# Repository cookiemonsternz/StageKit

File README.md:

# Stagekit

Stagekit is a 3D-printable, completely hand-solderable diy lighting previs kit. 

It consists of various fixtures, truss elements, and set dressing pieces, all modelled at a fairly accurate 1:10 scale. The truss pieces are modelled after standard Eurotruss, and the lights after various fixtures, but due to design requirements, sizing and design liberties have had to be taken. 

The inspiration for the design was really just the limited visualisation tools available for hobbyist lighting designers. There's certainly a lot of software, but much of it is prohibitively expensive, especially for students, then of course, comes the question of having software that can actually output to it. Guess what, you have to pay for that too. 

## Fixtures

Currently, Stagekit has 3 fixture designs available, but more designs are coming in the future.

| Fixture     | Estimated Material Cost (USD) | Images                               |
|-------------|-------------------------------| ------------------------------------ |
| RGB Par     | $4                            |  |
| RGB Tube    | $5                            |     |
| RGB Blinder | $4                            |  |

The RGB Blinder and RGB Tube both utilize neopixels, and the RGB Par uses a RGB Led. All fixtures use an ATTiny85 acting as an i2c slave, controlled by a RPi Zero 2 W or other i2c capable controller. The controller acts as an art net node, and sends i2c over 4 wire Molex Picoblade connectors, daisy chained together akin to DMX.

## Truss Pieces

There are currently four main truss pieces available, with more options in the future again.
All parts should be easily printable, and there are versions of each file which should be able to be printed without supports. 

Truss piece straight - 100mm

Truss piece corner

Truss base piece

Truss connector bracket

## Set elements

There are a variety of set pieces available.
Ashdown ABM-600 EVO IV:

Ampeg Classic 8x10 Cab:

Fender Rumble 100:

Markbass 1x15 cab:

Generic 4x10 cab:

Generic Roadcase:

Generic Wedge Monitor:

Generic Subwoofer:

Generic Line Array:

*Note: scale should be checked before printing, while this is to scale, it is very large*

Generic Fence:

Stage platform 1x1:

Stage platform 1x2:

Stage platform 2x2:

Stage stairs:

Finally, an example miniature stage mockup:

## Firmware

To program the ATTiny85 chips, you will need either a dedicated programmer or an Arduino Uno or similar. The source code for all of the lights can be found in the firmware directory.

Unfortunately, due to size and budget limitations, light addresses must be hardcoded into each chip individually. This means that when flashing firmware, ensure each light has a different address assigned, by editing the `.ino` file and changing the value of `I2C_SLAVE_ADDRESS` to any unused value between 0x01 and 0x7F before programming.

PCB Source files can be found in the respective folder (Blinder, RGB Par, RGB Tube) and all 3D models can be found inside the cad folder.

## PCB Pictures for Highway

RGB Par:

RGB Tube:

Blinder:

## BOM

Better formatted BOM's are also available at [this google sheet](https://docs.google.com/spreadsheets/d/1baBuS65jXXmk7wej5hXxSFTJ-pqP7fWwTh28TKW3xLs).

**RGB PAR**
| Item       | Part Name       | Quantity | Source     | Link                                                  | Unit Cost | Total Cost | Notes                                                                                                                                                                                            |
|------------|-----------------|----------|------------|-------------------------------------------------------|-----------|------------|--------------------------------------------------------------------------------------------------------------------------------------------------------------------------------------------------|
| U1         | ATTiny85        | 1        | Aliexpress | https://www.aliexpress.com/item/1005007400913382.html | 1.75      | 1.75       | Looking for cheaper ones                                                                                                                                                                         |
| D1         | RGB LED         | 1        | Aliexpress | https://www.aliexpress.com/item/1005005768279384.html | 0.46      | 0.46       | I have designed this for the 3x3w 6 pin rgb, as that is what I had on hand, but the 3x1w 6 pin rgb will almost certainly work as well, and the led driver does not even close to deliver 3 watts |
| R1         | 150Ω Resistor   | 1        | Aliexpress | https://www.aliexpress.com/item/1005001627995396.html | 0.02      | 0.02       | Comes in pack of 100, 1.65 per resistor value                                                                                                                                                    |
| R2, R3     | 100Ω Resistor   | 2        | Aliexpress | https://www.aliexpress.com/item/1005001627995396.html | 0.02      | 0.04       | Comes in pack of 100, 1.65 per resistor value                                                                                                                                                    |
| R4         | 10KΩ Resistor   | 1        | Aliexpress | https://www.aliexpress.com/item/1005001627995396.html | 0.02      | 0.02       | Comes in pack of 100, 1.65 per resistor value                                                                                                                                                    |
| J1, J3     | Molex Conn      | 2        | Aliexpress | https://aliexpress.com/item/4000127192324.html        | 0.06      | 0.12       | If you buy more than 50 you can bring this down to a total cost of 0.16                                                                                                                          |
| PCB        | PCB             | 1        | JLCPCB     | https://jlcpcb.com/                                   | 0.42      | 0.42       |                                                                                                                                                                                                  |
| CASEB      | Bottom Case     | 1        | 3D Printed | NA                                                    | 0.08      | 0.08       | around 4g of filament, if done through jlc3dp with standard resin, costs 0.36                                                                                                                    |
| CASET      | Top Case        | 1        | 3D Printed | NA                                                    | 0.04      | 0.04       | If printed on fdm printer, its approx 2g of filament, if ordered through jlcpcb with standard resin, cost 0.3 (min possible)                                                                     |
| PAPER      | Diffusion Paper | 1        | NA         | NA                                                    | NA        | NA         | The diffusion paper can be any semi transparent paper like material, I'm using white baking paper, and thus have ommitted the cost as it feels pointless to measure this                         |
| Total Cost |                 |          |            |                                                       |           |            |                                                                                                                                                                                                  |
|            |                 |          |            |                                                       |           | 2.95       | Economy of scale does come into play here, especially with the attiny and the pcbs                                                                                                               |

**RGB Tube**
| Item                   | Part Name       | Quantity | Source     | Link                                                  | Unit Cost | Total Cost | Notes                                                                                                                                                                                                                    |
|------------------------|-----------------|----------|------------|-------------------------------------------------------|-----------|------------|--------------------------------------------------------------------------------------------------------------------------------------------------------------------------------------------------------------------------|
| U1                     | ATTiny85        | 1        | Aliexpress | https://www.aliexpress.com/item/1005007400913382.html | 1.75      | 1.75       | Looking for cheaper ones                                                                                                                                                                                                 |
| R4                     | 10KΩ Resistor   | 1        | Aliexpress | https://www.aliexpress.com/item/1005001627995396.html | 0.02      | 0.02       | Comes in pack of 100, 1.65 per resistor value                                                                                                                                                                            |
| J1, J2                 | Molex Conn      | 2        | Aliexpress | https://aliexpress.com/item/4001254843951.html        | 0.04      | 0.08       | This is for 100 unfortunately, but I can't find anything else on aliexpress and lcsc shipping is insane                                                                                                                  |
| D1, D2, D3, D4, D5, D6 | Neopixel        | 6        | Aliexpress | https://www.aliexpress.com/item/4001345875756.html    | 0.03      | 0.18       | This is assuming ordering a batch of 100                                                                                                                                                                                 |
| PCB                    | PCB             | 1        | JLCPCB     | https://jlcpcb.com/                                   | 0.84      | 0.84       | Batch of five                                                                                                                                                                                                            |
| CASEB                  | Bottom Case     | 1        | 3D Printed | NA                                                    | NA        | NA         | Cura says 0g of filament lol, if done through jlc3dp with standard resin, cost 0.3                                                                                                                                       |
| CASET1                 | Top Case Body   | 1        | 3D Printed | NA                                                    | 0.05      | 0.05       | around 3g of filament, if done through jlc3dp with standard resin, costs 0.30. This piece includes the clamp connected to the print, but it can also be printed seperately                                               |
| CASET2                 | Top Case Cap    | 1        | 3D Printed | NA                                                    | NA        | NA         | Again, 0g of filament, will also cost 0.3 because that is the minimum cost                                                                                                                                               |
| TUBE                   | PMMA Tube       | 1        | Aliexpress | https://www.aliexpress.com/item/1005004505505004.html | 0.98      | 0.98       | OD 12mm, ID 10mm, 130mm long                                                                                                                                                                                             |
| PAPER                  | Diffusion Paper | 1        | NA         | NA                                                    | NA        | NA         | The diffusion paper can be any semi transparent paper like material, I'm not including this in mine as the pmma tube serves this purpose, but if you use acrylic for example, you may want to add some form of diffusion |
| Total Cost             |                 |          |            |                                                       |           |            |                                                                                                                                                                                                                          |
|                        |                 |          |            |                                                       |           | 3.9        | Economy of scale does come into play here, especially with the attiny and the pcbs                                                                                                                                       |

**RGB Blinder**
| Item       | Part Name       | Quantity | Source     | Link                                                  | Unit Cost | Total Cost | Notes                                                                                                                                                                      |
|------------|-----------------|----------|------------|-------------------------------------------------------|-----------|------------|----------------------------------------------------------------------------------------------------------------------------------------------------------------------------|
| U1         | ATTiny85        | 1        | Aliexpress | https://www.aliexpress.com/item/1005007400913382.html | 1.75      | 1.75       | Looking for cheaper ones                                                                                                                                                   |
| R4         | 10KΩ Resistor   | 1        | Aliexpress | https://www.aliexpress.com/item/1005001627995396.html | 0.02      | 0.02       | Comes in pack of 100, 1.65 per resistor value                                                                                                                              |
| J1, J2     | Molex Conn      | 2        | Aliexpress | https://aliexpress.com/item/4000127192324.html        | 0.06      | 0.12       | If you buy more than 50 you can bring this down to a total cost of 0.16                                                                                                    |
| D1, D2     | Neopixel        | 2        | Aliexpress | https://www.aliexpress.com/item/4001345875756.html    | 0.03      | 0.06       | This is assuming ordering a batch of 100                                                                                                                                   |
| PCB        | PCB             | 1        | JLCPCB     | https://jlcpcb.com/                                   | 0.82      | 0.82       | Batch of five                                                                                                                                                              |
| CASEB      | Bottom Case     | 1        | 3D Printed | NA                                                    | 0.08      | 0.08       | around 4g of filament, if done through jlc3dp with standard resin, costs 0.3 - This piece includes the clamp connected to the print, but it can also be printed seperately |
| CASET      | Top Case        | 1        | 3D Printed | NA                                                    | 0.06      | 0.06       | around 3g of filament, if done through jlc3dp with standard resin, costs 0.3                                                                                               |
| PAPER      | Diffusion Paper | 1        | NA         | NA                                                    | NA        | NA         | The diffusion paper can be any semi transparent paper like material, I would reccomend some form of diffusion for this light, as the raw leds look a bit ugly              |
| Total Cost |                 |          |            |                                                       |           |            |                                                                                                                                                                            |
|            |                 |          |            |                                                       |           | 2.91       | Economy of scale does come into play here, especially with the attiny and the pcbs                                                                                         |

**Total**

| Part Name           | Quantity | Source             | Link                                              | Unit Cost | Total Cost | Notes                                                                                                                                                         |
|---------------------|----------|--------------------|---------------------------------------------------|-----------|------------|---------------------------------------------------------------------------------------------------------------------------------------------------------------|
| RGB Par             | 12       | SEE INDIVIDUAL BOM | NA                                                | 2.95      | 35.4       | Looking for cheaper ones                                                                                                                                      |
| RGB Tube            | 12       | SEE INDIVIDUAL BOM | NA                                                | 3.9       | 46.8       | Comes in pack of 100, 1.65 per resistor value                                                                                                                 |
| RGB Blinder         | 6        | SEE INDIVIDUAL BOM | NA                                                | 2.91      | 17.46      | If you buy more than 50 you can bring this down to a total cost of 0.16                                                                                       |
| Cables              | 20       | Aliexpress         | https://aliexpress.com/item/1005007774081283.html | 0.184     | 3.68       | The diffusion paper can be any semi transparent paper like material, I would reccomend some form of diffusion for this light, as the raw leds look a bit ugly |
| ATTiny Programmer   | 1        | Aliexpress         | https://aliexpress.com/item/1005005704723470.html | 1.43      | 1.43       |                                                                                                                                                               |
| 3D Printer filament | 1        | Aliexpress         | https://aliexpress.com/item/1005006861804231.html | 26.33     | 26.33      | I am printing >1kg of material. This includes: 16 Truss Straight (800g) + 4 Truss Corner (172g) + Various other elements                                      |
| Total Cost          |          |                    |                                                   |           |            |                                                                                                                                                               |
|                     |          |                    |                                                   |           | 131.1      | Excl shipping                                                                                                                                                 |
|                     |          |                    |                                                   |           | 119.57     | Incl. Shipping - Aliexpress (93.72) - JLCPCB (25.85)                                                                                                          |

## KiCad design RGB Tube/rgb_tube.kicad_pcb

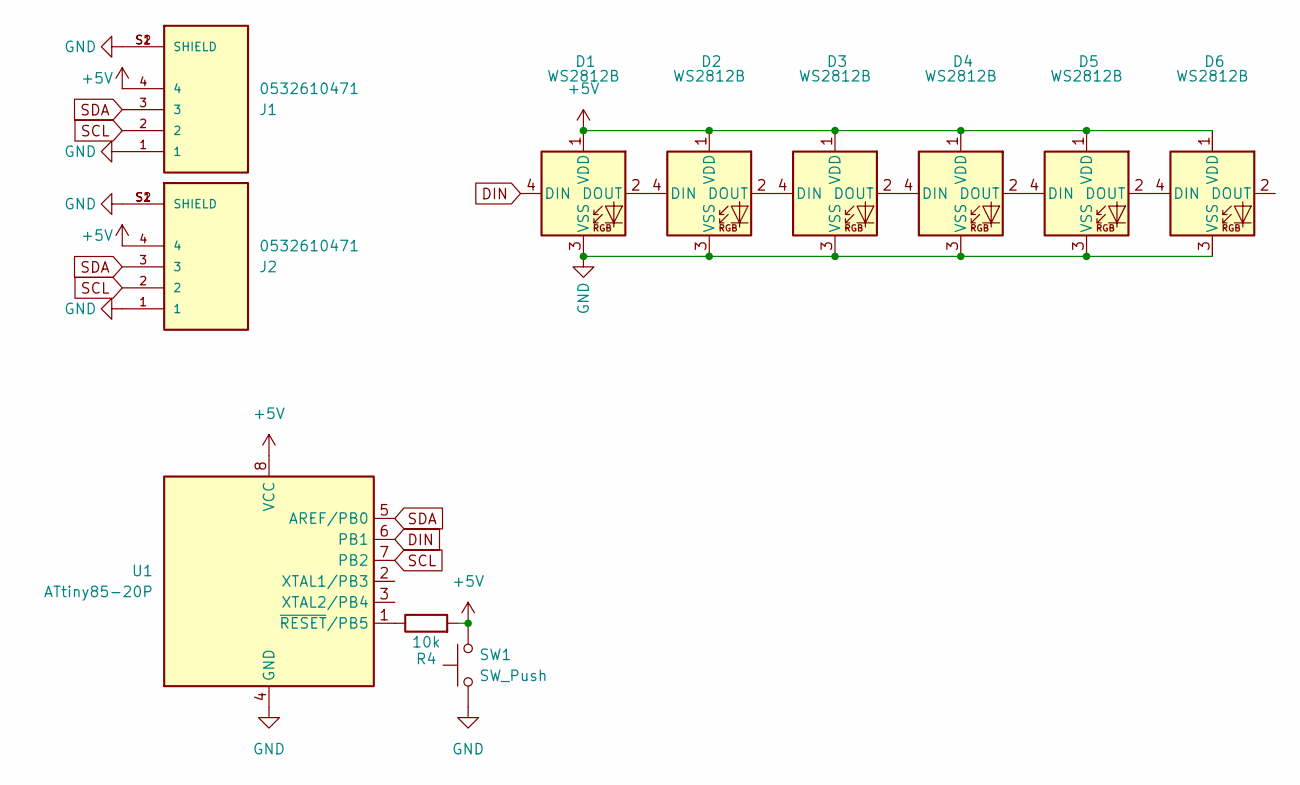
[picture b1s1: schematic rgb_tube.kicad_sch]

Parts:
D1, D2, D3, D4, D5, D6: WS2812B; LED_WS2812B_PLCC4_5.0x5.0mm_P3.2mm
J1, J2: 0532610471; MOLEX_0532610471; PARTREV J
R4: 10k; R_0805_2012Metric
SW1: SW_Push; PinHeader_1x02_P2.54mm_Vertical
U1: ATtiny85-20P; DIP-8_W7.62mm

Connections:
+5V: D1.1 (VDD), D2.1 (VDD), D3.1 (VDD), D4.1 (VDD), D5.1 (VDD), D6.1 (VDD), J1.4, J2.4, R4.2, SW1.2, U1.8 (VCC)
DIN: D1.4 (DIN), U1.6 (PB1)
GND: D1.3 (VSS), D2.3 (VSS), D3.3 (VSS), D4.3 (VSS), D5.3 (VSS), D6.3 (VSS), J1.1, J1.S1 (SHIELD), J1.S2 (SHIELD), J2.1, J2.S1 (SHIELD), J2.S2 (SHIELD), SW1.1, U1.4 (GND)
unnamed: D1.2 (DOUT), D2.4 (DIN)
unnamed: D2.2 (DOUT), D3.4 (DIN)
unnamed: D3.2 (DOUT), D4.4 (DIN)
unnamed: D4.2 (DOUT), D5.4 (DIN)
unnamed: D5.2 (DOUT), D6.4 (DIN)
unnamed: R4.1, U1.1 (~RESET/PB5)
SCL: J1.2, J2.2, U1.7 (PB2)
SDA: J1.3, J2.3, U1.5 (AREF/PB0)

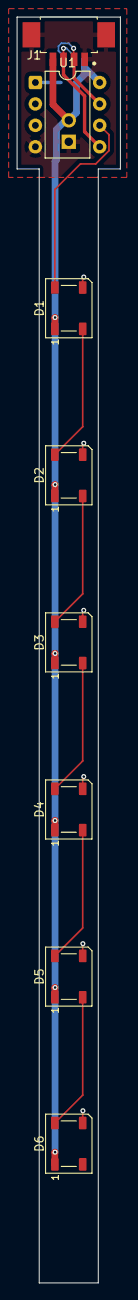
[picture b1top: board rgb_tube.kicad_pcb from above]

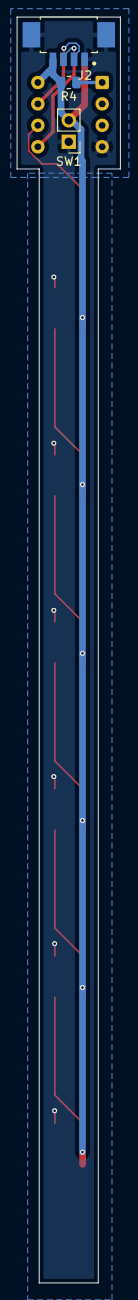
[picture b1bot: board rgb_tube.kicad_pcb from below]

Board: 2 copper layers, 12.2 x 150.0 mm, 11 parts (3 on the bottom side), 11 nets.

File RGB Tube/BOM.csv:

Item,Part Name,Quantity,Source,Link,Unit Cost,Total Cost,Notes
U1,ATTiny85,1,Aliexpress,https://www.aliexpress.com/item/1005007400913382.html,1.75,1.75,Looking for cheaper ones
R4,10KΩ Resistor,1,Aliexpress,https://www.aliexpress.com/item/1005001627995396.html,0.02,0.02,"Comes in pack of 100, 1.65 per resistor value"
"J1, J2",Molex Conn,2,Aliexpress,https://aliexpress.com/item/4001254843951.html,0.04,0.08,"This is for 100 unfortunately, but I can't find anything else on aliexpress and lcsc shipping is insane"
"D1, D2, D3, D4, D5, D6",Neopixel,6,Aliexpress,https://www.aliexpress.com/item/4001345875756.html,0.03,0.18,This is assuming ordering a batch of 100
PCB,PCB,1,JLCPCB,https://jlcpcb.com/,0.84,0.84,Batch of five
CASEB,Bottom Case,1,3D Printed,NA,NA,NA,"Cura says 0g of filament lol, if done through jlc3dp with standard resin, cost 0.3"
CASET1,Top Case Body,1,3D Printed,NA,0.05,0.05,"around 3g of filament, if done through jlc3dp with standard resin, costs 0.30. This piece includes the clamp connected to the print, but it can also be printed seperately"
CASET2,Top Case Cap,1,3D Printed,NA,NA,NA,"Again, 0g of filament, will also cost 0.3 because that is the minimum cost"
TUBE,PMMA Tube,1,Aliexpress,https://www.aliexpress.com/item/1005004505505004.html,0.98,0.98,"OD 12mm, ID 10mm, 130mm long"
PAPER,Diffusion Paper,1,NA,NA,NA,NA,"The diffusion paper can be any semi transparent paper like material, I'm not including this in mine as the pmma tube serves this purpose, but if you use acrylic for example, you may want to add some form of diffusion"
Total Cost,,,,,,,
,,,,,,3.9,"Economy of scale does come into play here, especially with the attiny and the pcbs"

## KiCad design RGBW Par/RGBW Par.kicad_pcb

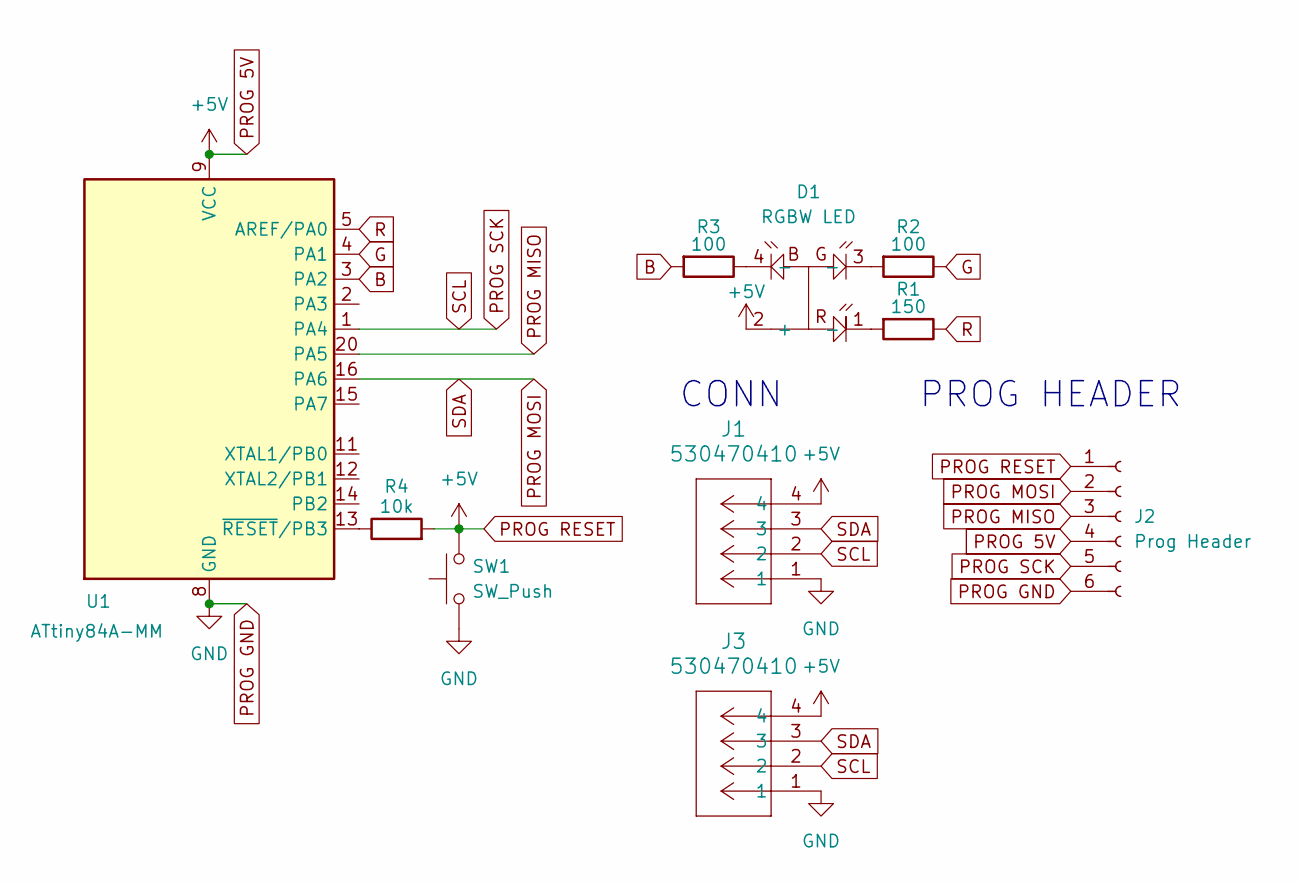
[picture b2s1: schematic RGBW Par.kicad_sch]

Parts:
D1: RGBW LED; XL-3528RGBW-HM
J1, J3: 530470410; Molex_PicoBlade_53047-0410_1x04_P1.25mm_Vertical
J2: Prog Header; PinHeader_1x06_P2.54mm_Vertical
R1: 150; R_0201_0603Metric
R2, R3: 100; R_0201_0603Metric
R4: 10k; R_0201_0603Metric
SW1: SW_Push; PinHeader_1x02_P2.54mm_Vertical
U1: ATtiny84A-MM; QFN-20-1EP_3x3mm_P0.45mm_EP1.6x1.6mm

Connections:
B: R3.2, U1.3 (PA2)
G: R2.1, U1.4 (PA1)
unnamed: D1.1 (-), R1.2
unnamed: D1.3 (-), R2.2
unnamed: D1.4 (-), R3.1
unnamed: R4.1, U1.13 (~RESET/PB3)
PROG 5V: D1.2 (+), J1.4, J2.1, J2.4, J3.4, R4.2, SW1.2, U1.9 (VCC)
PROG GND: J1.1, J2.6, J3.1, SW1.1, U1.8 (GND), U1.21 (GND)
PROG MISO: J2.3, U1.20 (PA5)
PROG MOSI: J1.3, J2.2, J3.3, U1.16 (PA6)
PROG SCK: J1.2, J2.5, J3.2, U1.1 (PA4)
R: R1.1, U1.5 (AREF/PA0)

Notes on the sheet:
CONN
PROG HEADER

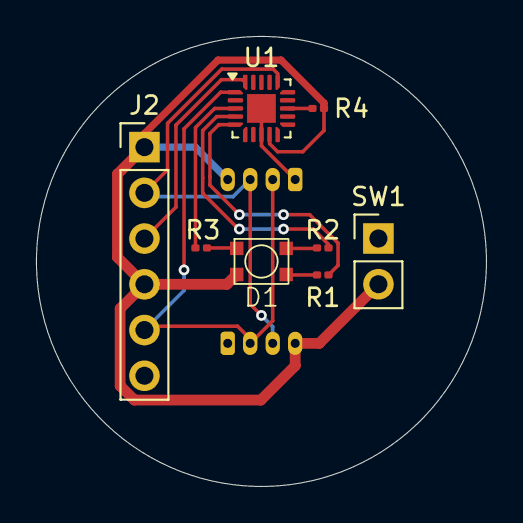
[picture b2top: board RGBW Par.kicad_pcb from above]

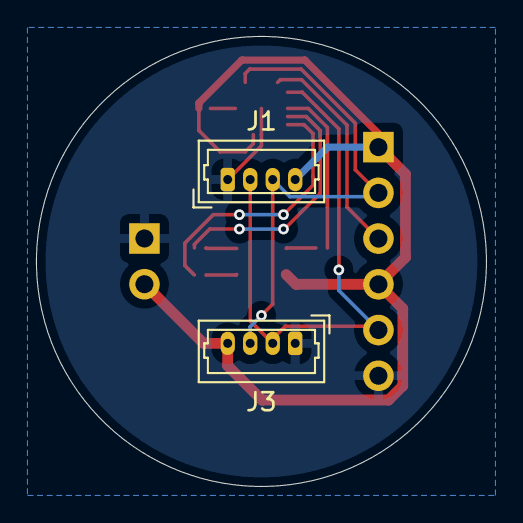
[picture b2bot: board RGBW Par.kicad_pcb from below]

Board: 2 copper layers, 25.0 x 25.0 mm, 10 parts (2 on the bottom side), 12 nets.

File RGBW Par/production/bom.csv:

Designator,Footprint,Quantity,Value,LCSC Part #
D1,XL-3528RGBW-HM,1,RGBW LED,
"J1, J3",Molex_PicoBlade_53047-0410_1x04_P1.25mm_Vertical,2,530470410,
J2,PinHeader_1x06_P2.54mm_Vertical,1,Prog Header,
R1,0201,1,150,
"R2, R3",0201,2,100,
R4,0201,1,10k,
SW1,PinHeader_1x02_P2.54mm_Vertical,1,SW_Push,
U1,QFN-20-1EP_3x3mm_P0.45mm_EP1.6x1.6mm,1,ATtiny84A-MM,

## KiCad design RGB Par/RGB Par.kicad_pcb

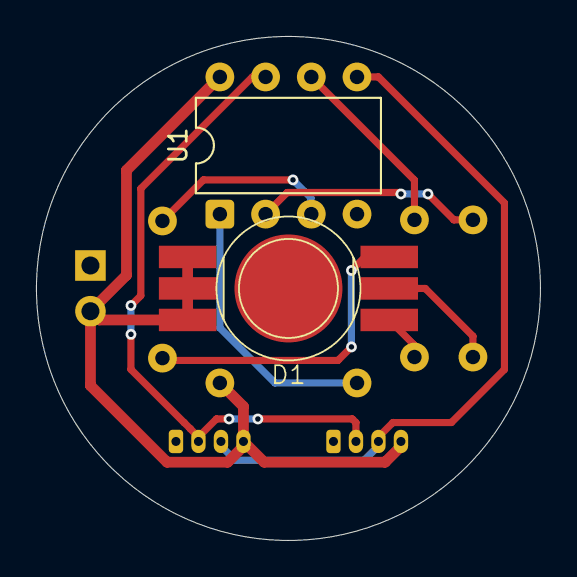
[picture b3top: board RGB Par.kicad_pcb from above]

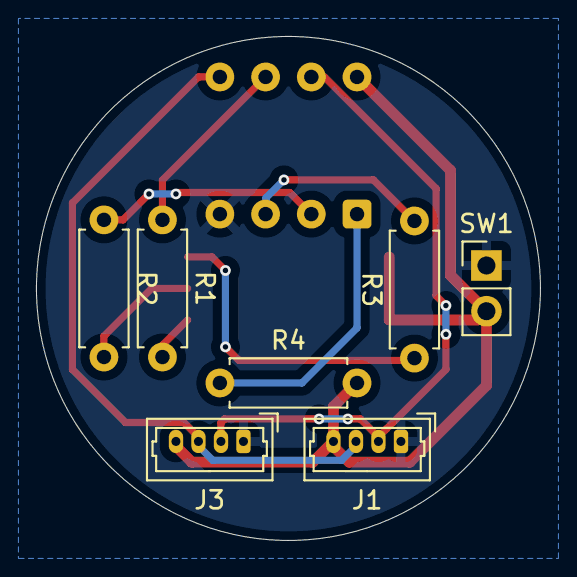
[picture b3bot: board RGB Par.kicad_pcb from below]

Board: 2 copper layers, 28.0 x 28.0 mm, 9 parts (7 on the bottom side), 11 nets.

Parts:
D1: rgb_led
J1, J3: 530470410; Molex_PicoBlade_53047-0410_1x04_P1.25mm_Vertical
R1: 150; R_Axial_DIN0207_L6.3mm_D2.5mm_P7.62mm_Horizontal
R2, R3: 100; R_Axial_DIN0207_L6.3mm_D2.5mm_P7.62mm_Horizontal
R4: 10k; R_Axial_DIN0207_L6.3mm_D2.5mm_P7.62mm_Horizontal
SW1: SW_Push; PinHeader_1x02_P2.54mm_Vertical
U1: ATtiny85-20P; DIP-8_W7.62mm

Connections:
+5V: D1.1 (+), D1.2 (+), D1.3 (+), J1.4, J3.4, R4.2, SW1.2, U1.8 (VCC)
B: R3.2, U1.3 (XTAL2/PB4)
G: R2.1, U1.2 (XTAL1/PB3)
GND: J1.1, J3.1, SW1.1, U1.4 (GND)
unnamed: D1.4 (-), R3.1
unnamed: D1.5 (-), R2.2
unnamed: D1.6 (-), R1.2
unnamed: R4.1, U1.1 (~RESET/PB5)
R: R1.1, U1.6 (PB1)
SCL: J1.2, J3.2, U1.7 (PB2)
SDA: J1.3, J3.3, U1.5 (AREF/PB0)

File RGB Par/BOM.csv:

Item,Part Name,Quantity,Source,Link,Unit Cost,Total Cost,Notes
U1,ATTiny85,1,Aliexpress,https://www.aliexpress.com/item/1005007400913382.html,1.75,1.75,Looking for cheaper ones
D1,RGB LED,1,Aliexpress,https://www.aliexpress.com/item/1005005768279384.html,0.46,0.46,"I have designed this for the 3x3w 6 pin rgb, as that is what I had on hand, but the 3x1w 6 pin rgb will almost certainly work as well, and the led driver does not even close to deliver 3 watts"
R1,150Ω Resistor,1,Aliexpress,https://www.aliexpress.com/item/1005001627995396.html,0.02,0.02,"Comes in pack of 100, 1.65 per resistor value"
"R2, R3",100Ω Resistor,2,Aliexpress,https://www.aliexpress.com/item/1005001627995396.html,0.02,0.04,"Comes in pack of 100, 1.65 per resistor value"
R4,10KΩ Resistor,1,Aliexpress,https://www.aliexpress.com/item/1005001627995396.html,0.02,0.02,"Comes in pack of 100, 1.65 per resistor value"
"J1, J3",Molex Conn,2,LCSC,https://lcsc.com/product-detail/Wire-To-Board-Connector_MOLE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,0.0975,0.195,If you buy more than 50 you can bring this down to a total cost of 0.16
PCB,PCB,1,JLCPCB,https://jlcpcb.com/,0.42,0.42,
CASEB,Bottom Case,1,3D Printed,NA,0.08,0.08,"around 4g of filament, if done through jlc3dp with standard resin, costs 0.36"
CASET,Top Case,1,3D Printed,NA,0.04,0.04,"If printed on fdm printer, its approx 2g of filament, if ordered through jlcpcb with standard resin, cost 0.3 (min possible)"
PAPER,Diffusion Paper,1,NA,NA,NA,NA,"The diffusion paper can be any semi transparent paper like material, I'm using white baking paper, and thus have ommitted the cost as it feels pointless to measure this"
Total Cost,,,,,,,
,,,,,,3.025,"Economy of scale does come into play here, especially with the attiny and the pcbs"

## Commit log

2025-06-13 Init Commit
2025-06-14 straight 100mm done, journal 1 done
2025-06-15 Auto stash before merge of "master" and "origin/master"
2025-06-16 RGB Par V1
2025-06-16 RGB Par v1 it. 2
2025-06-16 rgb par v2
2025-06-17 rgb par case
2025-06-17 fix images and add note
2025-06-19 Rename rgbw par, update boms, add blinder and export cad for all lights
2025-06-25 blinder, journals, actually add journal metadata :skull:
2025-07-13 mainly cad work with set pieces + journalling, add firmware + journals
2025-07-17 add readme and prep for review
2025-07-17 add total time count
2025-07-17 finish prep for review, add basic demo control firmware
